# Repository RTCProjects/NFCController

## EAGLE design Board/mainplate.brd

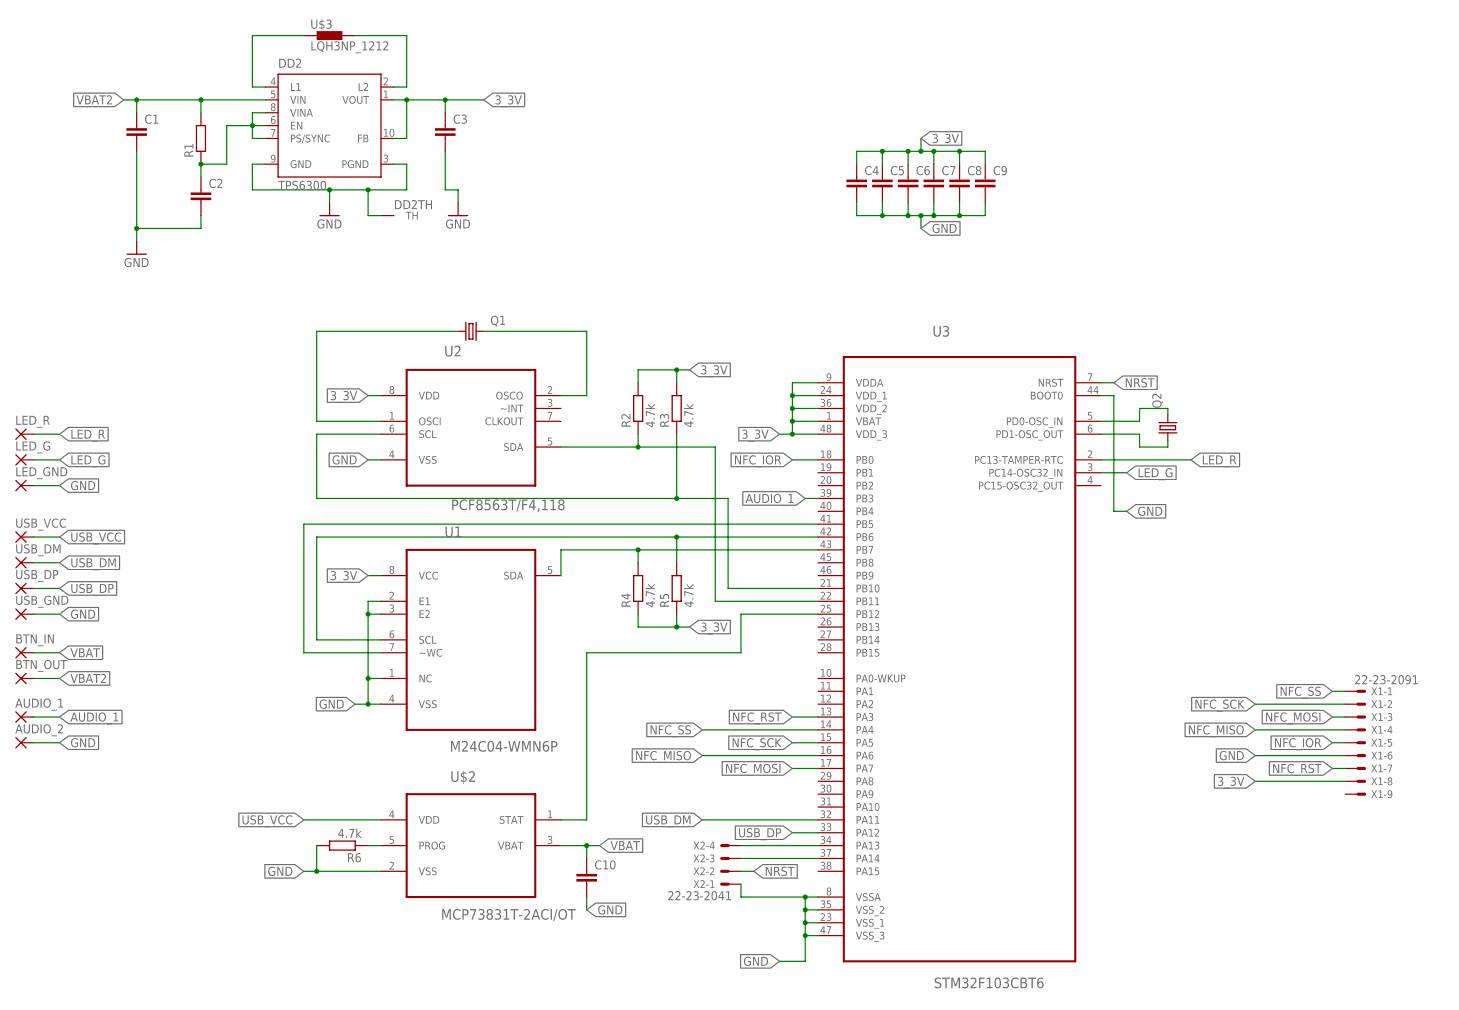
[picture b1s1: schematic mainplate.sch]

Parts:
AUDIO_1, AUDIO_2: 2,54/1,0
BTN_IN: 2,54/1,0
BTN_OUT: 2,54/1,0
C1, C2, C3, C4, C5, C6, C7, C8, C9, C10: C-EUC0603; C0603
DD2: TPS6300; DRC-S-PVSON-N10
LED_G: 2,54/1,0
LED_GND: 2,54/1,0
LED_R: 2,54/1,0
Q1: KX-327-NHT; 3.2X1.5
Q2: KX-K; 11.4X4.5
R1: R-EU_R0603; R0603
R2, R3, R4, R5, R6: 4.7k; R0603
U1: M24C04-WMN6P; SOIC127P600X175-8N
U2: PCF8563T/F4,118; SOIC127P600X175-8N
U3: STM32F103CBT6; QFP50P900X900X160-48N
U$2: MCP73831T-2ACI/OT; SOT95P280X145-5N
U$3: LQH3NP_1212
USB_DM: 2,54/1,0
USB_DP: 2,54/1,0
USB_GND: 2,54/1,0
USB_VCC: 2,54/1,0
X1: 22-23-2091
X2: 22-23-2041

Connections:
3_3V: C3.1, C4.1, C5.1, C6.1, C7.1, C8.1, C9.1, DD2.1 (VOUT), DD2.10 (FB), R2.2, R3.2, R4.1, R5.1, U1.8 (VCC), U2.8 (VDD), U3.1 (VBAT), U3.9 (VDDA), U3.24 (VDD_1), U3.36 (VDD_2), U3.48 (VDD_3), X1.8
AUDIO_1: AUDIO_1.1, U3.39 (PB3)
EE_WC: U1.7 (~WC), U3.41 (PB5)
GND: AUDIO_2.1, C1.2, C2.2, C3.2, C4.2, C5.2, C6.2, C7.2, C8.2, C9.2, C10.2, DD2.3 (PGND), DD2.9 (GND), DD2.TH, LED_GND.1, R6.2, U1.1 (NC), U1.2 (E1), U1.3 (E2), U1.4 (VSS), U2.4 (VSS), U3.8 (VSSA), U3.23 (VSS_1), U3.35 (VSS_2), U3.44 (BOOT0), U3.47 (VSS_3), U$2.2 (VSS), USB_GND.1, X1.6, X2.1
LED_G: LED_G.1, U3.3 (PC14-OSC32_IN)
LED_R: LED_R.1, U3.2 (PC13-TAMPER-RTC)
unnamed: Q2.2, U3.5 (PD0-OSC_IN)
unnamed: Q2.1, U3.6 (PD1-OSC_OUT)
unnamed: DD2.4 (L1), U$3.P$1 (1)
unnamed: R2.1, U2.5 (SDA), U3.22 (PB11)
unnamed: DD2.2 (L2), U$3.P$2 (2)
unnamed: R3.1, U2.6 (SCL), U3.21 (PB10)
unnamed: R4.2, U1.5 (SDA), U3.43 (PB7)
unnamed: C2.1, DD2.6 (EN), DD2.7 (PS/SYNC), DD2.8 (VINA), R1.1
unnamed: R5.2, U1.6 (SCL), U3.42 (PB6)
unnamed: Q1.1, U2.1 (OSCI)
unnamed: Q1.2, U2.2 (OSCO)
unnamed: R6.1, U$2.5 (PROG)
unnamed: U3.34 (PA13), X2.4
unnamed: U3.37 (PA14), X2.3
unnamed: U3.25 (PB12), U$2.1 (STAT)
NFC_IOR: U3.18 (PB0), X1.5
NFC_MISO: U3.16 (PA6), X1.4
NFC_MOSI: U3.17 (PA7), X1.3
NFC_RST: U3.13 (PA3), X1.7
NFC_SCK: U3.15 (PA5), X1.2
NFC_SS: U3.14 (PA4), X1.1
NRST: U3.7 (NRST), X2.2
USB_DM: U3.32 (PA11), USB_DM.1
USB_DP: U3.33 (PA12), USB_DP.1
USB_VCC: U$2.4 (VDD), USB_VCC.1
VBAT: BTN_IN.1, C10.1, U$2.3 (VBAT)
VBAT2: BTN_OUT.1, C1.1, DD2.5 (VIN), R1.2

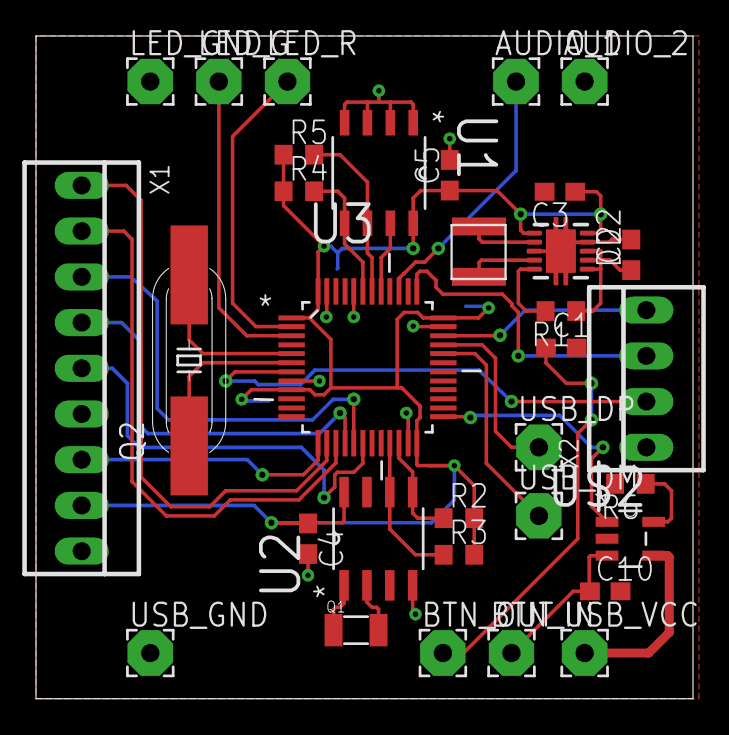
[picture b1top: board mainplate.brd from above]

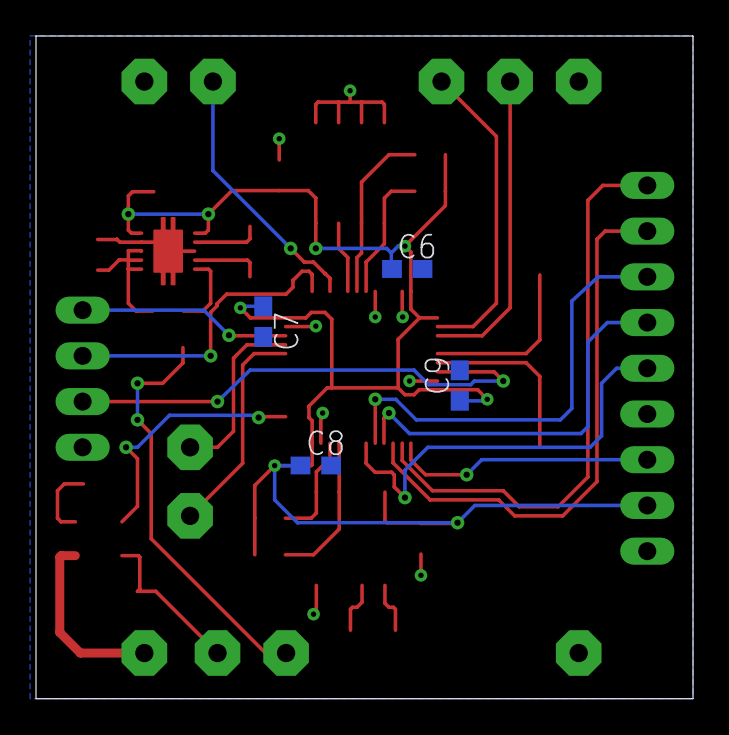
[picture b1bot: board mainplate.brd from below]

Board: 2 copper layers, 36.5 x 36.8 mm, 37 parts (4 on the bottom side), 33 nets.

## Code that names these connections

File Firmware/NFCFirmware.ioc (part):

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Mcu.Name=STM32F103C(8-B)Tx
Mcu.Package=LQFP48
Mcu.UserName=STM32F103C8Tx
PA11.Mode=Device
PA11.Signal=USB_DM
PA12.Mode=Device
PA12.Signal=USB_DP
PA3.GPIOParameters=GPIO_Label
PA3.GPIO_Label=NFC_RST
PA3.Signal=GPIO_Output
PA4.Mode=NSS_Signal_Hard_Output
PA4.Signal=SPI1_NSS
PA5.Mode=Full_Duplex_Master
PA5.Signal=SPI1_SCK
PA6.Mode=Full_Duplex_Master
PA6.Signal=SPI1_MISO
PA7.Mode=Full_Duplex_Master
PA7.Signal=SPI1_MOSI
PB10.Mode=I2C
PB10.Signal=I2C2_SCL
PB11.Mode=I2C
PB11.Signal=I2C2_SDA
PB6.Mode=I2C
PB6.Signal=I2C1_SCL
PB7.Mode=I2C
PB7.Signal=I2C1_SDA
PD0-OSC_IN.Mode=HSE-External-Oscillator
PD0-OSC_IN.Signal=RCC_OSC_IN
PD1-OSC_OUT.Mode=HSE-External-Oscillator
PD1-OSC_OUT.Signal=RCC_OSC_OUT
RCC.HSE_VALUE=16000000
RCC.SYSCLKFreq_VALUE=48000000
RCC.SYSCLKSource=RCC_SYSCLKSOURCE_PLLCLK

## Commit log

2018-04-19 Inital commit
2018-04-19 Process commit
2018-04-19 plate process
2018-04-20 First release version

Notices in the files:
parts and their libraries:
crystal-geyer_V1_0: Copyright: Geyer-Electronic
